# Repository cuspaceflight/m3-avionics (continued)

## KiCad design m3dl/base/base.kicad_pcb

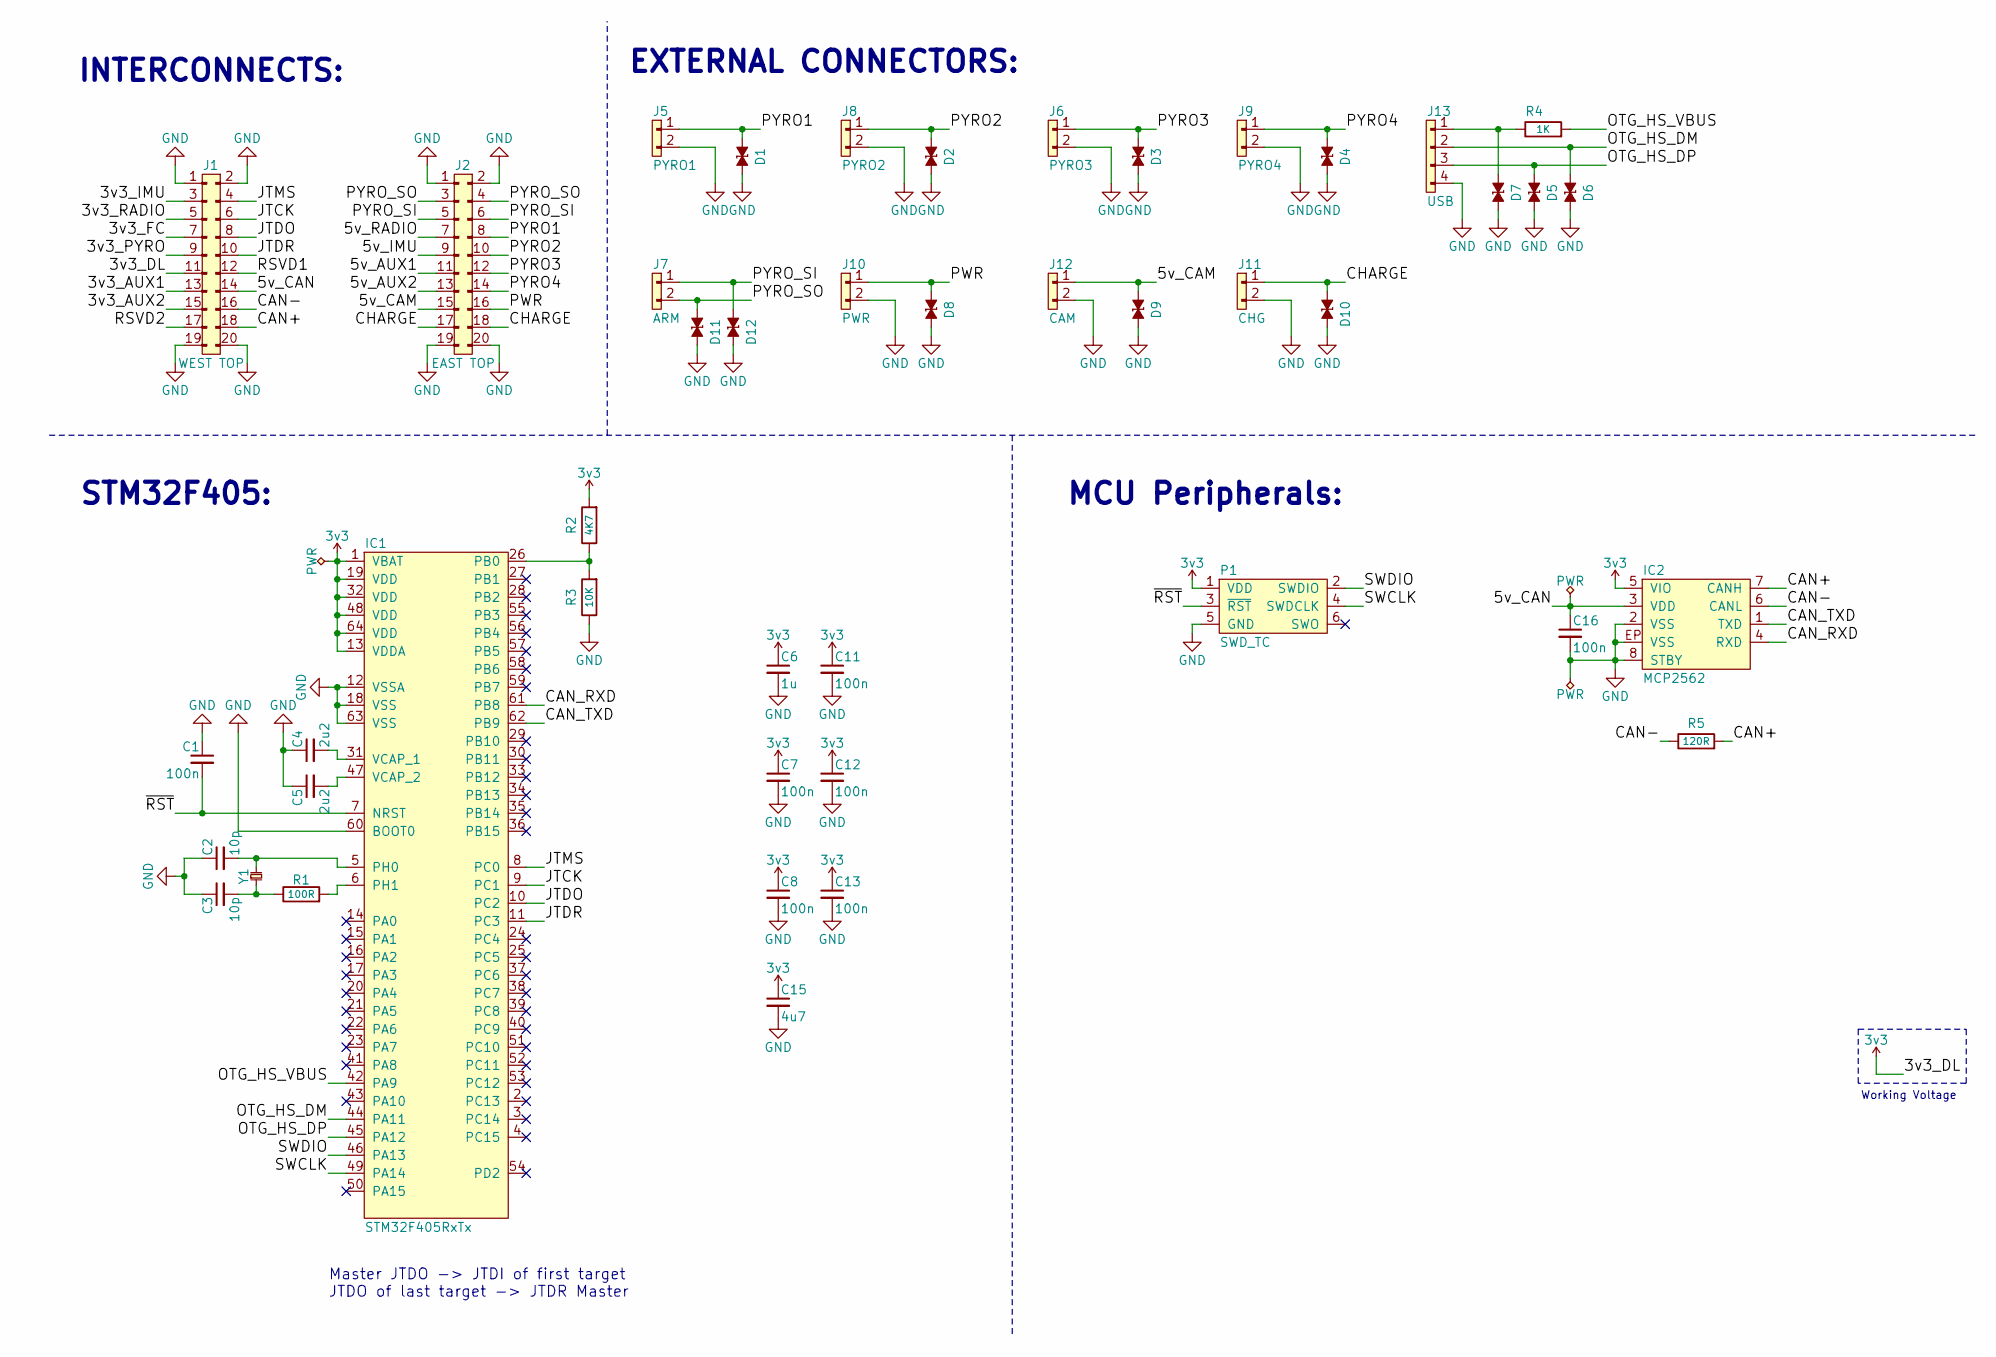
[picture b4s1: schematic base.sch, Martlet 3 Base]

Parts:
C1, C7, C8, C11, C12, C13, C16: 100n; C_0603; Farnell 2496834
C2, C3: 10p; C_0603; Farnell 2309035
C4, C5: 2u2; C_0603; Farnell 1797012
C6: 1u; C_0603; Farnell 1865556
C15: 4u7; C_0603; Farnell 2496930
D1, D2, D3, D4, D5, D6, D7, D8, D9, D10, D11, D12: ESD_DIODE; 0402; Farnell 2368169
IC1: STM32F405RxTx; LQFP-64; Farnell 2064363
IC2: MCP2562; DFN-8-EP-MICROCHIP; Farnell 2448755
J1: WEST TOP; TFML-110-02-L-D
J2: EAST TOP; TFML-110-02-L-D
J5: PYRO1; B02B-PASK; Farnell 1830734
J6: PYRO3; B02B-PASK; Farnell 1830734
J7: ARM; B02B-PASK; Farnell 1830734
J8: PYRO2; B02B-PASK; Farnell 1830734
J9: PYRO4; B02B-PASK; Farnell 1830734
J10: PWR; B02B-PASK; Farnell 1830734
J11: CHG; B02B-PASK; Farnell 1830734
J12: CAM; B02B-PASK; Farnell 1830734
J13: USB; B04B-PASK; Farnell 1830737
P1: SWD_TC; TC2030-NL
R1: 100R; R_0603; Farnell 2502395
R2: 4K7; R_0603; Farnell 2502463
R3: 10K; R_0603; Farnell 9238603
R4: 1K; R_0603; Farnell 2309108
R5: 120R; R_0603; Farnell 9238379
Y1: 26MHz; XTAL-20x16; Farnell 2506952

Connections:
3v3: C6.1, C7.1, C8.1, C11.1, C12.1, C13.1, C15.1, IC1.1 (VBAT), IC1.13 (VDDA), IC1.19 (VDD), IC1.32 (VDD), IC1.48 (VDD), IC1.64 (VDD), IC2.5 (VIO), J1.11, P1.1 (VDD), R2.2
/3v3_AUX1: J1.13
/3v3_AUX2: J1.15
/3v3_FC: J1.7
/3v3_IMU: J1.3
/3v3_PYRO: J1.9
/3v3_RADIO: J1.5
/5v_AUX1: J2.11
/5v_AUX2: J2.13
/5v_CAM: D9.1, J2.15, J12.1
/5v_CAN: C16.1, IC2.3 (VDD), J1.14
/5v_IMU: J2.9
/5v_RADIO: J2.7
/CAN+: IC2.7 (CANH), J1.18, R5.2
/CAN-: IC2.6 (CANL), J1.16, R5.1
/CAN_RXD: IC1.61 (PB8), IC2.4 (RXD)
/CAN_TXD: IC1.62 (PB9), IC2.1 (TXD)
/CHARGE: D10.1, J2.17, J2.18, J11.1
/JTCK: IC1.9 (PC1), J1.6
/JTDO: IC1.10 (PC2), J1.8
/JTDR: IC1.11 (PC3), J1.10
/JTMS: IC1.8 (PC0), J1.4
/OTG_HS_DM: D6.1, IC1.44 (PA11), J13.2
/OTG_HS_DP: D5.1, IC1.45 (PA12), J13.3
/OTG_HS_VBUS: IC1.42 (PA9), R4.2
/PWR: D8.1, J2.16, J10.1
/PYRO1: D1.1, J2.8, J5.1
/PYRO2: D2.1, J2.10, J8.1
/PYRO3: D3.1, J2.12, J6.1
/PYRO4: D4.1, J2.14, J9.1
/PYRO_SI: D12.1, J2.5, J2.6, J7.1
/PYRO_SO: D11.1, J2.3, J2.4, J7.2
/RSVD1: J1.12
/RSVD2: J1.17
/SWCLK: IC1.49 (PA14), P1.4 (SWDCLK)
/SWDIO: IC1.46 (PA13), P1.2 (SWDIO)
/~RST: C1.2, IC1.7 (NRST), P1.3 (~RST)
GND: C1.1, C2.1, C3.1, C4.1, C5.1, C6.2, C7.2, C8.2, C11.2, C12.2, C13.2, C15.2, C16.2, D1.2, D2.2, D3.2, D4.2, D5.2, D6.2, D7.2, D8.2, D9.2, D10.2, D11.2, D12.2, IC1.12 (VSSA), IC1.18 (VSS), IC1.60 (BOOT0), IC1.63 (VSS), IC2.2 (VSS), IC2.8 (STBY), IC2.EP (VSS), J1.1, J1.2, J1.19, J1.20, J2.1, J2.2, J2.19, J2.20, J5.2, J6.2, J8.2, J9.2, J10.2, J11.2, J12.2, J13.4, P1.5 (GND), R3.1
unnamed: C2.2, IC1.5 (PH0), Y1.2
unnamed: C3.2, R1.1, Y1.1
unnamed: C4.2, IC1.31 (VCAP_1)
unnamed: C5.2, IC1.47 (VCAP_2)
unnamed: D7.1, J13.1, R4.1
unnamed: IC1.6 (PH1), R1.2
unnamed: IC1.26 (PB0), R2.1, R3.2

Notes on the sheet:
STM32F405:
MCU Peripherals:
Working Voltage
INTERCONNECTS:
EXTERNAL CONNECTORS:
Master JTDO -> JTDI of first target JTDO of last target -> JTDR Master

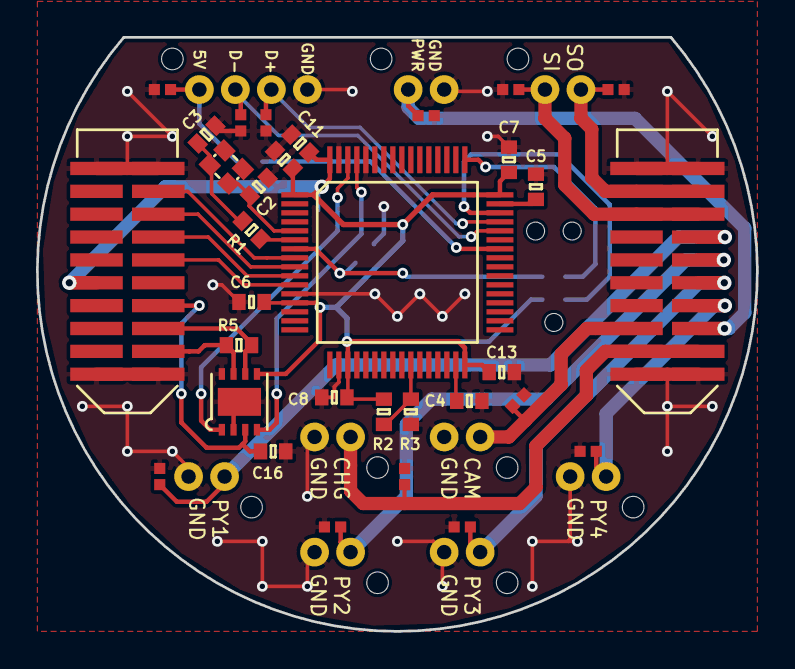
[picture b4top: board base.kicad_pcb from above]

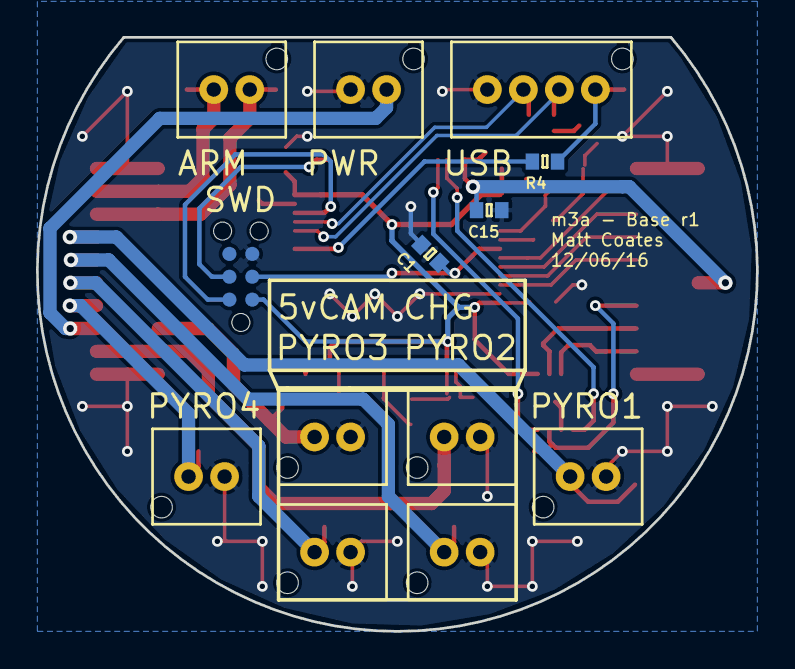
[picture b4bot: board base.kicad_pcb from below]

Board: 2 copper layers, 40.0 x 33.0 mm, 45 parts (13 on the bottom side), 33 nets.

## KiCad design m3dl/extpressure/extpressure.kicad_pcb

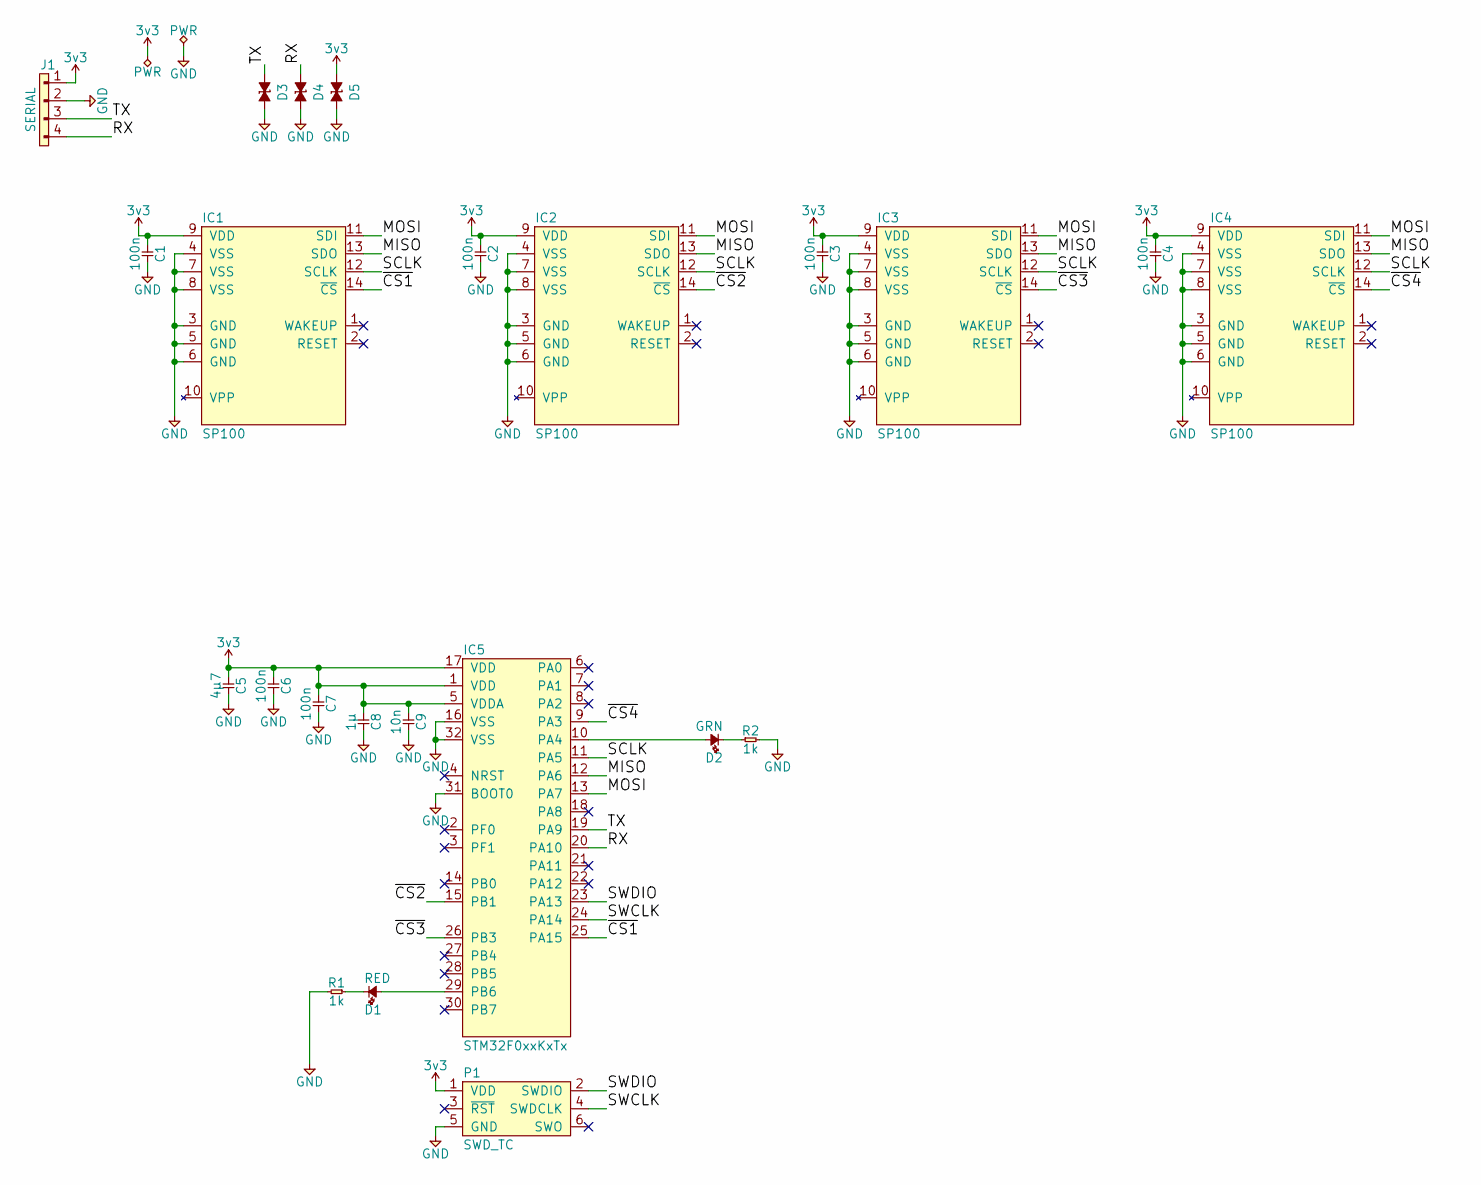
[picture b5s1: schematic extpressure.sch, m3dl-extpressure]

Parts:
C1, C2, C3, C4, C6, C7: 100n; 0402; Farnell 2496771
C5: 4µ7; 0402; Farnell 2426952
C8: 1µ; 0402; Farnell 2496814
C9: 10n; 0402; Farnell 2210793
D1: RED; 0603-LED; Farnell 2290329
D2: GRN; 0603-LED; Farnell 2290328
D3, D4, D5: ESD_DIODE; 0402; Farnell 2368169
IC1, IC2, IC3, IC4: SP100; Farnell 1845345
IC5: STM32F0xxKxTx; LQFP-32; Farnell 2333141
J1: SERIAL; S04B-PASK-2; Farnell 1830749
P1: SWD_TC; TC2030-NL
R1, R2: 1k; 0402; Farnell 2447120

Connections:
3v3: C1.1, C2.1, C3.1, C4.1, C5.1, C6.1, C7.1, C8.1, C9.1, D5.1, IC1.9 (VDD), IC2.9 (VDD), IC3.9 (VDD), IC4.9 (VDD), IC5.1 (VDD), IC5.5 (VDDA), IC5.17 (VDD), J1.1, P1.1 (VDD)
/MISO: IC1.13 (SDO), IC2.13 (SDO), IC3.13 (SDO), IC4.13 (SDO), IC5.12 (PA6)
/MOSI: IC1.11 (SDI), IC2.11 (SDI), IC3.11 (SDI), IC4.11 (SDI), IC5.13 (PA7)
/RX: D4.1, IC5.20 (PA10), J1.4
/SCLK: IC1.12 (SCLK), IC2.12 (SCLK), IC3.12 (SCLK), IC4.12 (SCLK), IC5.11 (PA5)
/SWCLK: IC5.24 (PA14), P1.4 (SWDCLK)
/SWDIO: IC5.23 (PA13), P1.2 (SWDIO)
/TX: D3.1, IC5.19 (PA9), J1.3
/~CS1: IC1.14 (~CS), IC5.25 (PA15)
/~CS2: IC2.14 (~CS), IC5.15 (PB1)
/~CS3: IC3.14 (~CS), IC5.26 (PB3)
/~CS4: IC4.14 (~CS), IC5.9 (PA3)
GND: C1.2, C2.2, C3.2, C4.2, C5.2, C6.2, C7.2, C8.2, C9.2, D3.2, D4.2, D5.2, IC1.3 (GND), IC1.4 (VSS), IC1.5 (GND), IC1.6 (GND), IC1.7 (VSS), IC1.8 (VSS), IC2.3 (GND), IC2.4 (VSS), IC2.5 (GND), IC2.6 (GND), IC2.7 (VSS), IC2.8 (VSS), IC3.3 (GND), IC3.4 (VSS), IC3.5 (GND), IC3.6 (GND), IC3.7 (VSS), IC3.8 (VSS), IC4.3 (GND), IC4.4 (VSS), IC4.5 (GND), IC4.6 (GND), IC4.7 (VSS), IC4.8 (VSS), IC5.16 (VSS), IC5.31 (BOOT0), IC5.32 (VSS), J1.2, P1.5 (GND), R1.2, R2.2
unnamed: D1.1, R1.1
unnamed: D1.2, IC5.29 (PB6)
unnamed: D2.1, R2.1
unnamed: D2.2, IC5.10 (PA4)

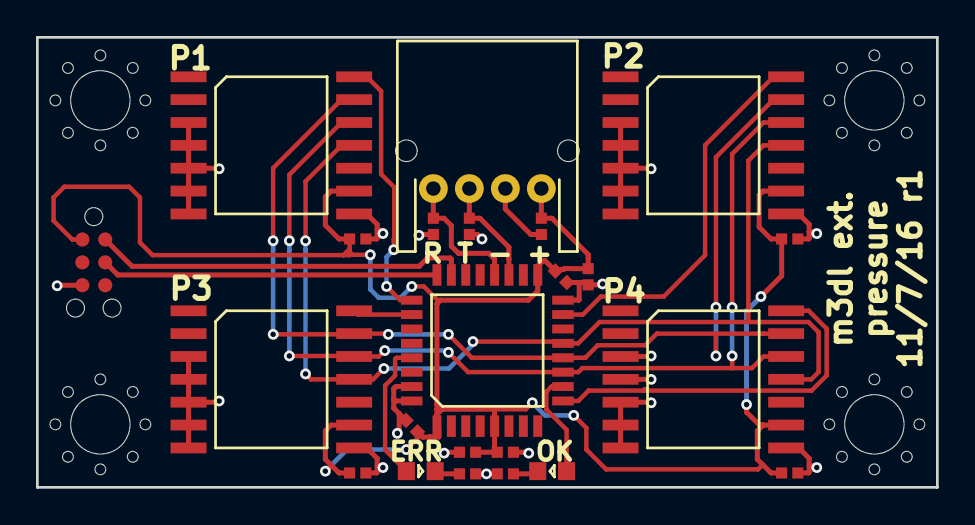
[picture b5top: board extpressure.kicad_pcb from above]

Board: 2 copper layers, 50.0 x 25.0 mm, 23 parts (0 on the bottom side), 17 nets.

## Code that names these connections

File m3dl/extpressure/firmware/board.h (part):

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/*
 *  GPIOA setup:
 *
 * PA0  - PIN0                         (unused).
 * PA1  - PIN1                         (unused).
 * PA2  - PIN2                         (unused).
 * PA3  - CS4                          (output, floating).
 * PA4  - LED_GRN                      (output, startlow, floating).
 * PA5  - SCLK                         (af0).
 * PA6  - MISO                         (af0).
 * PA7  - MOSI                         (af0).
 * PA8  - PIN8                         (unused).
 * PA9  - TX                           (af1).
 * PA10 - RX                           (af1).
 * PA11 - PIN11                        (unused).
 * PA12 - PIN12                        (unused).
 * PA13 - SWDIO                        (af0).
 * PA14 - SWCLK                        (af0, pulldown).
 * PA15 - CS1                          (output, floating).
*/
#define VAL_GPIOA_MODER                (PIN_MODE_INPUT(GPIOA_PIN0) | \
                                        PIN_MODE_INPUT(GPIOA_PIN1) | \
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/*
 *  GPIOB setup:
 *
 * PB0  - PIN0                         (unused).
 * PB1  - CS2                          (output, floating).
 * PB2  - PIN2                         (unused).
 * PB3  - CS3                          (output, floating).
 * PB4  - PIN4                         (unused).
 * PB5  - PIN5                         (unused).
 * PB6  - LED_RED                      (output, startlow, floating).
 * PB7  - PIN7                         (unused).
 * PB8  - PIN8                         (unused).
 * PB9  - PIN9                         (unused).
 * PB10 - PIN10                        (unused).
 * PB11 - PIN11                        (unused).
 * PB12 - PIN12                        (unused).
 * PB13 - PIN13                        (unused).
 * PB14 - PIN14                        (unused).
 * PB15 - PIN15                        (unused).
*/
#define VAL_GPIOB_MODER                (PIN_MODE_INPUT(GPIOB_PIN0) | \
                                        PIN_MODE_OUTPUT(GPIOB_CS2) | \
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/*
 *  GPIOC setup:
 *
 * PC0  - PIN0                         (unused).
 * PC1  - PIN1                         (unused).
 * PC2  - PIN2                         (unused).
 * PC3  - PIN3                         (unused).
 * PC4  - PIN4                         (unused).
 * PC5  - PIN5                         (unused).
 * PC6  - PIN6                         (unused).
 * PC7  - PIN7                         (unused).
 * PC8  - PIN8                         (unused).
 * PC9  - PIN9                         (unused).
 * PC10 - PIN10                        (unused).
 * PC11 - PIN11                        (unused).
 * PC12 - PIN12                        (unused).
 * PC13 - PIN13                        (unused).
 * PC14 - PIN14                        (unused).
 * PC15 - PIN15                        (unused).
*/
#define VAL_GPIOC_MODER                (PIN_MODE_INPUT(GPIOC_PIN0) | \
                                        PIN_MODE_INPUT(GPIOC_PIN1) | \
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 *
 * PD0  - PIN0                         (unused).
 * PD1  - PIN1                         (unused).
 * PD2  - PIN2                         (unused).
 * PD3  - PIN3                         (unused).
 * PD4  - PIN4                         (unused).
 * PD5  - PIN5                         (unused).
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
